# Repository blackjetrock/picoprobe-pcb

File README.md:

# picoprobe-pcb
PCB to hold a picoprobe and victim Pico, or program an external Pico

This PCB holds two Picos, one programmed as a PicoProbe and one the target Pico
that the picoprobe will program.
There are jumpers for the SWD signals and they can be used to program 
and external Pico on a different PCB.

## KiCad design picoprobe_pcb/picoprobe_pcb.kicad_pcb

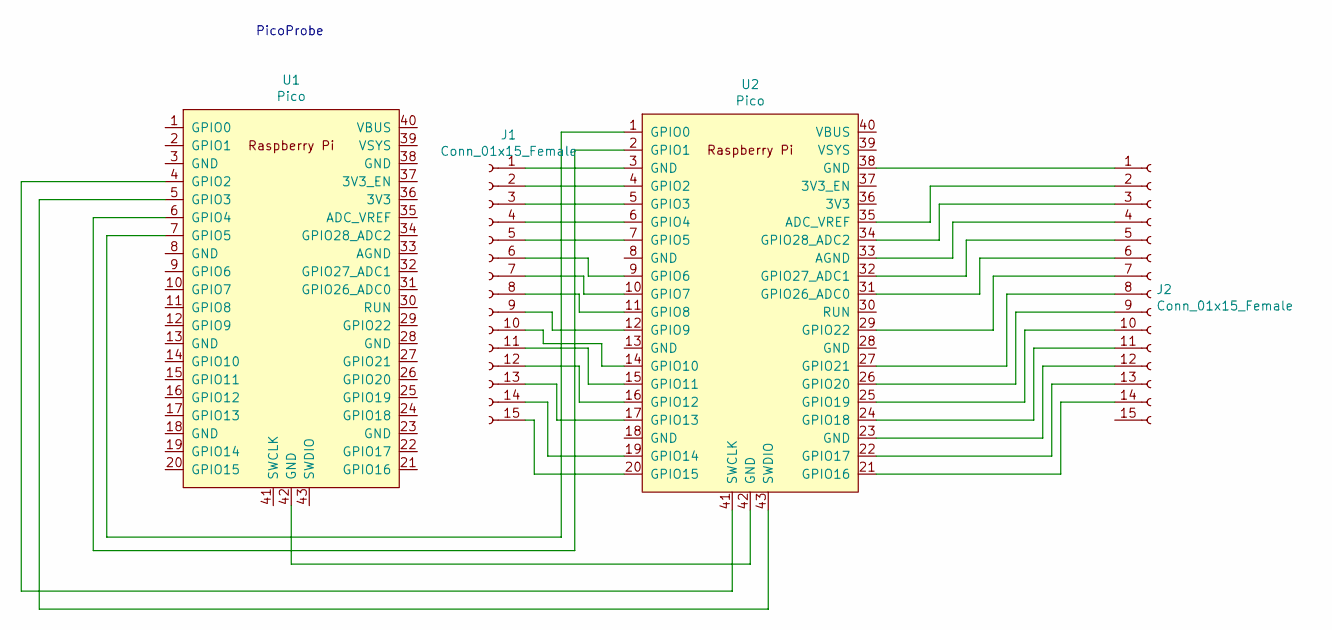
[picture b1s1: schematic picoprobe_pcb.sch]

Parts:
J1, J2: Conn_01x15_Female; PinHeader_1x15_P2.54mm_Vertical
U1, U2: Pico; RPi_Pico_SMD_TH

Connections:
unnamed: J1.1, U2.3 (GND)
unnamed: J1.2, U2.4 (GPIO2)
unnamed: J1.3, U2.5 (GPIO3)
unnamed: J1.4, U2.6 (GPIO4)
unnamed: J1.5, U2.7 (GPIO5)
unnamed: J1.6, U2.9 (GPIO6)
unnamed: J1.7, U2.10 (GPIO7)
unnamed: J1.8, U2.11 (GPIO8)
unnamed: J1.9, U2.12 (GPIO9)
unnamed: J1.10, U2.14 (GPIO10)
unnamed: J1.11, U2.15 (GPIO11)
unnamed: J1.12, U2.16 (GPIO12)
unnamed: J1.13, U2.17 (GPIO13)
unnamed: J1.14, U2.19 (GPIO14)
unnamed: J1.15, U2.20 (GPIO15)
unnamed: J2.1, U2.38 (GND)
unnamed: J2.2, U2.35 (ADC_VREF)
unnamed: J2.3, U2.34 (GPIO28_ADC2)
unnamed: J2.4, U2.33 (AGND)
unnamed: J2.5, U2.32 (GPIO27_ADC1)
unnamed: J2.6, U2.31 (GPIO26_ADC0)
unnamed: J2.7, U2.29 (GPIO22)
unnamed: J2.8, U2.27 (GPIO21)
unnamed: J2.9, U2.26 (GPIO20)
unnamed: J2.10, U2.25 (GPIO19)
unnamed: J2.11, U2.24 (GPIO18)
unnamed: J2.12, U2.23 (GND)
unnamed: J2.13, U2.22 (GPIO17)
unnamed: J2.14, U2.21 (GPIO16)
unnamed: U1.4 (GPIO2), U2.41 (SWCLK)
unnamed: U1.5 (GPIO3), U2.43 (SWDIO)
unnamed: U1.6 (GPIO4), U2.2 (GPIO1)
unnamed: U1.7 (GPIO5), U2.1 (GPIO0)
unnamed: U1.42 (GND), U2.42 (GND)

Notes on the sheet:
PicoProbe

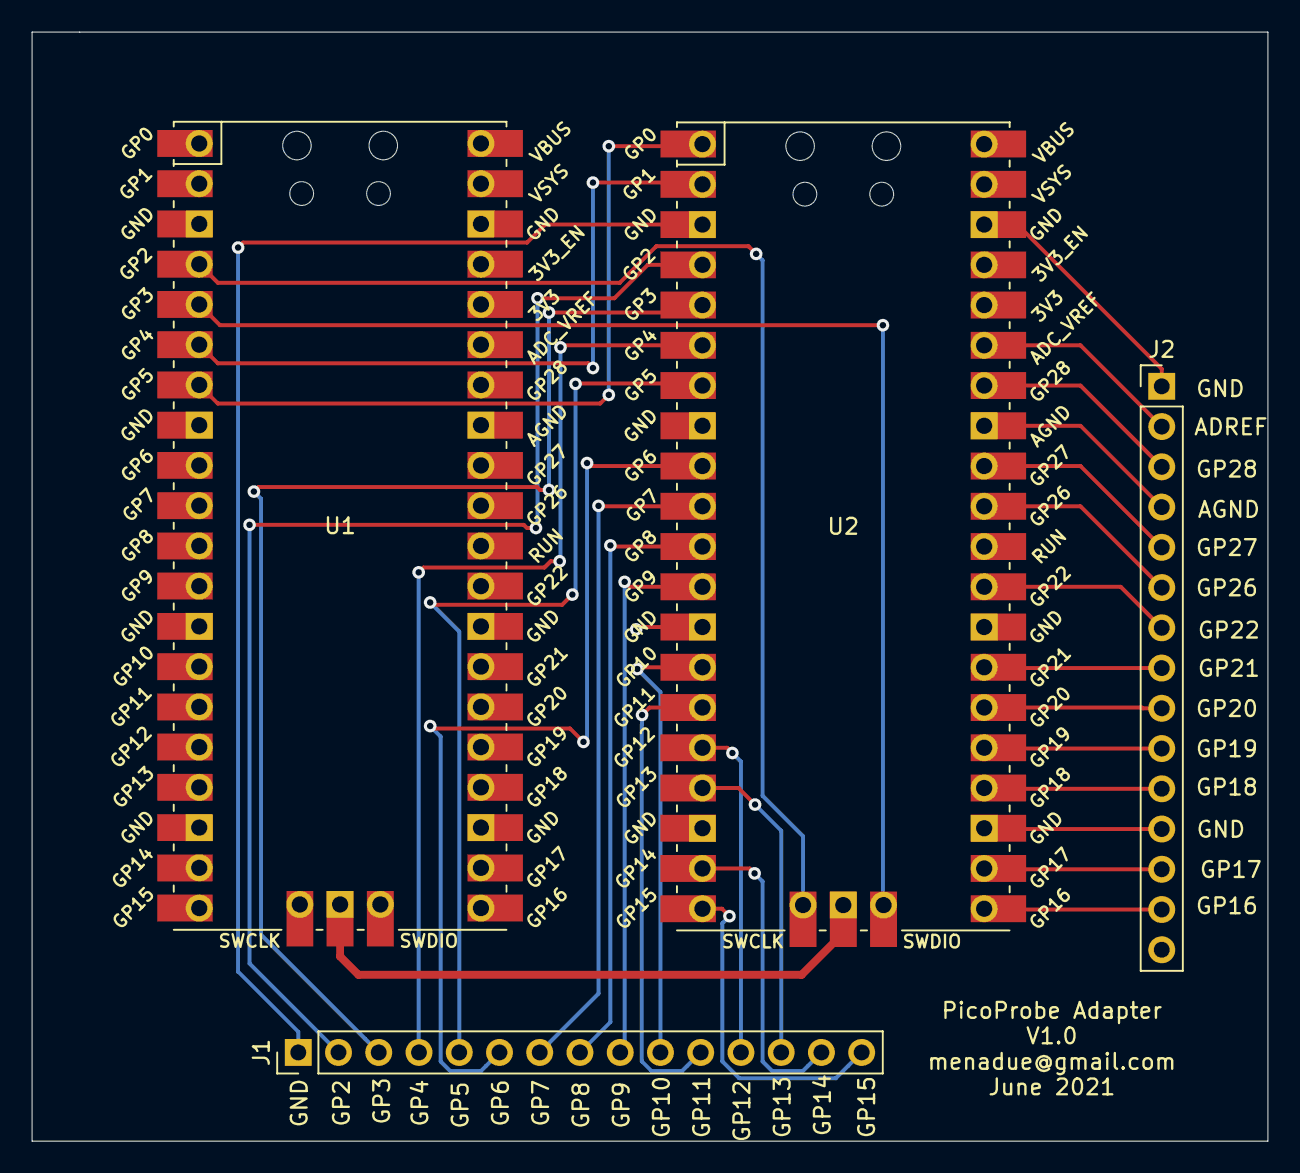
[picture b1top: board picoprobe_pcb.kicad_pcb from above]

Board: 2 copper layers, 78.0 x 70.0 mm, 4 parts (0 on the bottom side), 34 nets.
